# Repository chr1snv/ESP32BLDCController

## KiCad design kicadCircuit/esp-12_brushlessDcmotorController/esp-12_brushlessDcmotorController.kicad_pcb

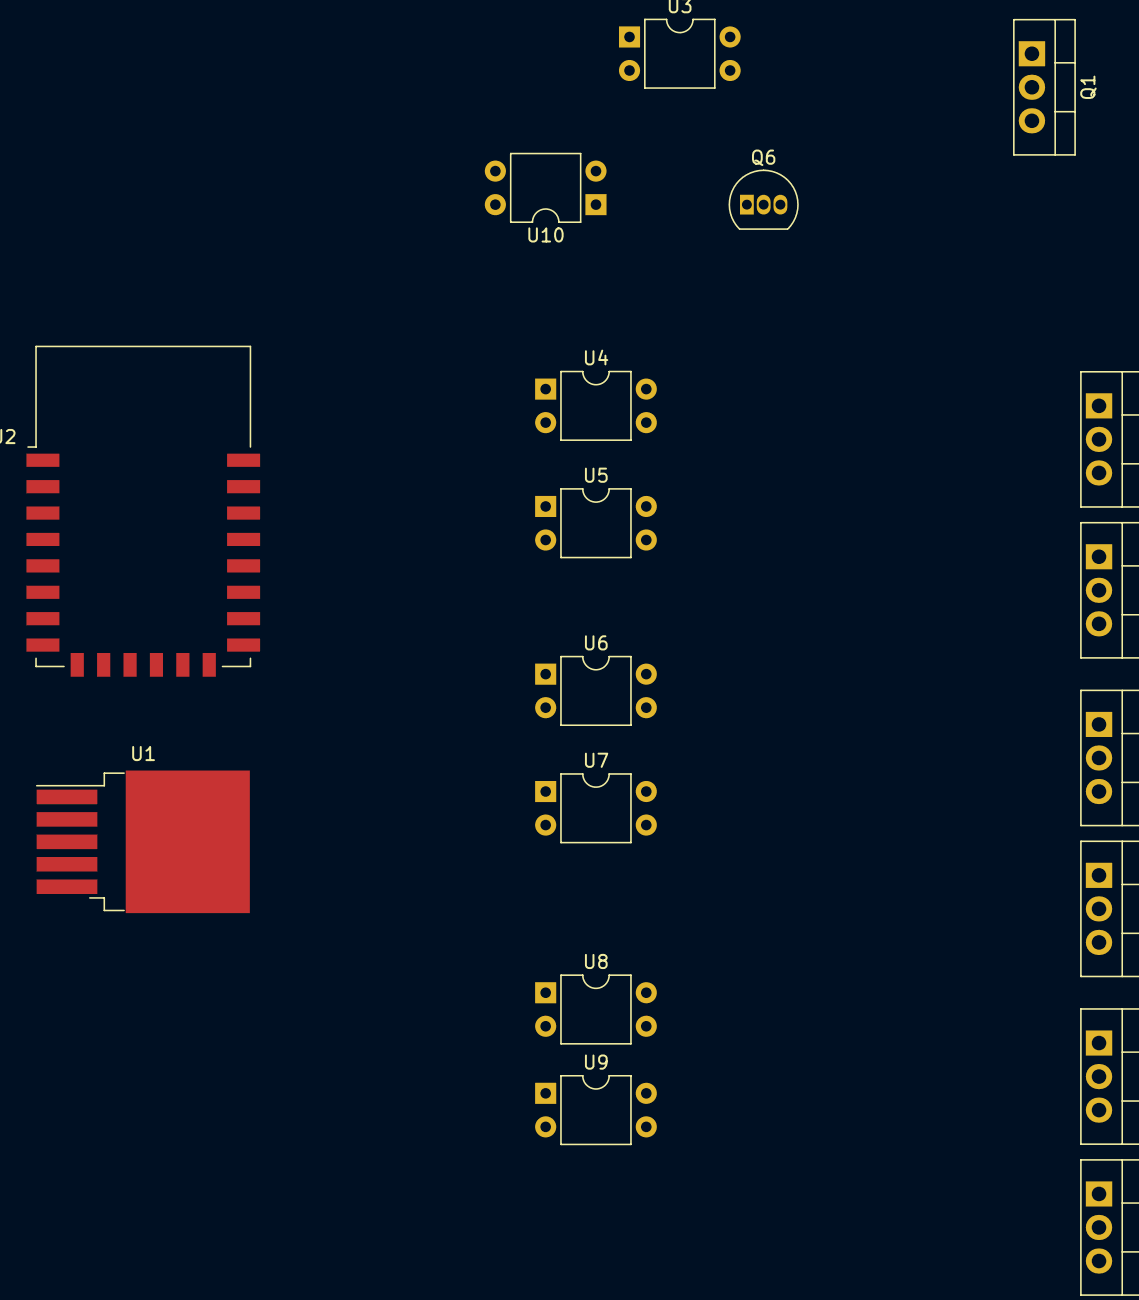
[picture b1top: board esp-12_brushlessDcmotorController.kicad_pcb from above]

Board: 2 copper layers, 18 parts (0 on the bottom side), 22 nets, no tracks yet.

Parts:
Q1, Q2, Q3, Q4, Q5, Q7, Q8: IRF3205; TO-220-3_Vertical
Q6: 2N7000; TO-92_Inline
U1: LM2576HVS-5; TO-263-5_TabPin3
U2: ESP-12E
U3, U4, U5, U6, U7, U8, U9, U10: PC817; DIP-4_W7.62mm

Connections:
+5V: U1.2, U2.8
+12V: Q4.2, Q5.2, Q8.2, U1.1, U3.4
GND: Q1.3, Q2.3, Q7.3, U1.3, U2.15, U10.2, U10.3
unnamed: Q2.2, Q4.3
unnamed: Q3.2, Q5.3
unnamed: Q7.2, Q8.3
unnamed: Q1.1, U3.3
unnamed: Q2.1, U5.3
unnamed: Q3.1, U7.3
unnamed: Q4.1, U4.3
unnamed: Q5.1, U6.3
unnamed: Q6.1, U10.1
unnamed: Q7.1, U9.3
unnamed: Q8.1, U8.3
unnamed: U2.4, U9.1
unnamed: U2.5, U6.1
unnamed: U2.6, U7.1
unnamed: U2.7, U8.1
unnamed: U2.16, U4.1
unnamed: U2.19, U5.1
unnamed: U2.20, U3.1
unnamed: U2.17, U10.4

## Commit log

2024-02-15 esp32 node mcu brushless n channel mosfet driver arduino code and kicad electrical schematic
